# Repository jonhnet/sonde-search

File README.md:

# sonde-search
a couple dorks trying to break into the easiest hobby ever

## Conda environment

The conda environment is pinned in `environment.yml` (versions only, no build hashes — portable across platforms).

Create a fresh env:
```bash
mamba env create -n sondesearch -f environment.yml
```

Sync an existing env to match (adds new deps, removes removed ones):
```bash
mamba env update -n sondesearch -f environment.yml --prune
```

After changing deps locally, regenerate the lock and commit it:
```bash
conda env export --no-builds | sed '/^prefix:/d' > environment.yml
```

## Tests

From the repo root:
```bash
pytest
```
Each subproject (`aprs-backhaul/`, `analyzers/paneltest/`, `website/backend/`) can also be tested independently from its own directory.

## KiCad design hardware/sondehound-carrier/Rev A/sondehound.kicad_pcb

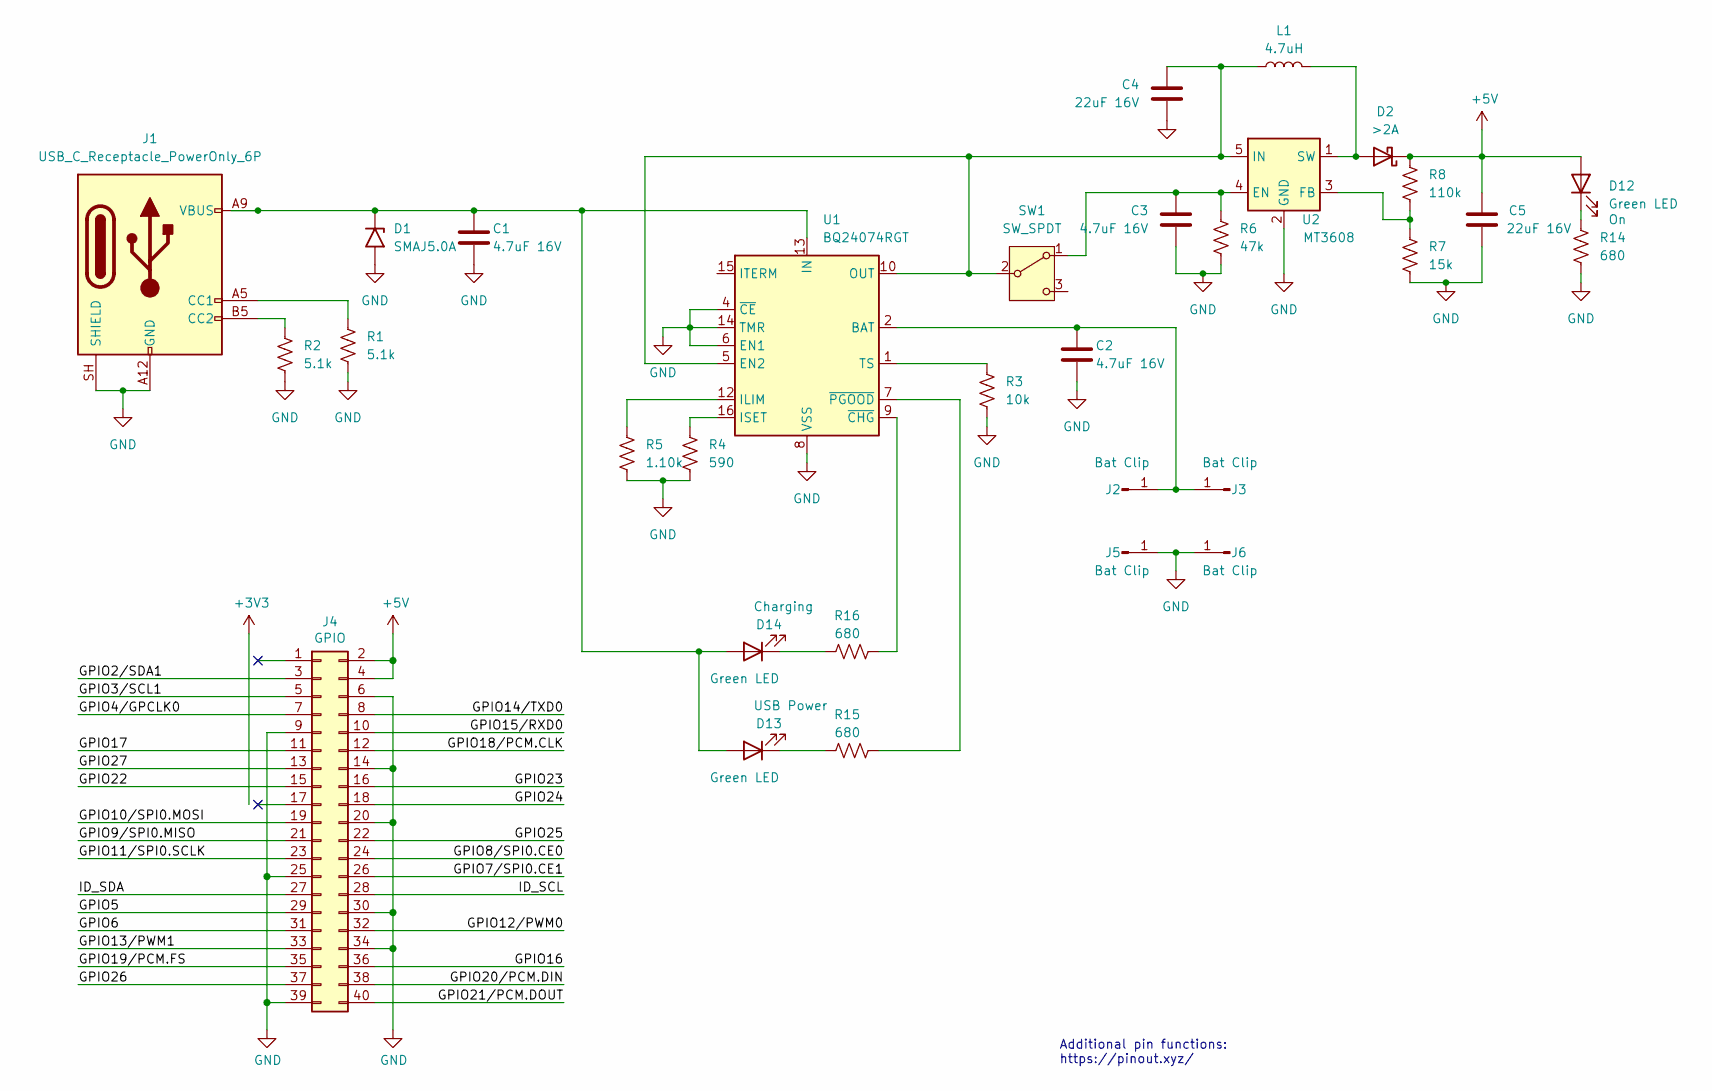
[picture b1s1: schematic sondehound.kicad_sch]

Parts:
C1, C2, C3: 4.7uF 16V; C_0603_1608Metric_Pad1.08x0.95mm_HandSolder
C4, C5: 22uF 16V; C_1210_3225Metric_Pad1.33x2.70mm_HandSolder
D1: SMAJ5.0A; D_SMA
D2: >2A; D_SMA_Handsoldering
D12, D13, D14: Green LED; LED_0603_1608Metric_Pad1.05x0.95mm_HandSolder
J1: USB_C_Receptacle_PowerOnly_6P; USB_C_Receptacle_GCT_USB4125-xx-x_6P_TopMnt_Horizontal
J2, J3, J5, J6: Bat Clip; BatteryClip_Keystone_54_D16-19mm
J4: GPIO; PinSocket_2x20_P2.54mm_Vertical
L1: 4.7uH; L_Chilisin_BMRB00050518-B
R1, R2: 5.1k; R_0603_1608Metric_Pad0.98x0.95mm_HandSolder
R3: 10k; R_0603_1608Metric_Pad0.98x0.95mm_HandSolder
R4: 590; R_0603_1608Metric_Pad0.98x0.95mm_HandSolder
R5: 1.10k; R_0603_1608Metric_Pad0.98x0.95mm_HandSolder
R6: 47k; R_0603_1608Metric_Pad0.98x0.95mm_HandSolder
R7: 15k; R_0603_1608Metric_Pad0.98x0.95mm_HandSolder
R8: 110k; R_0603_1608Metric_Pad0.98x0.95mm_HandSolder
R14, R15, R16: 680; R_0603_1608Metric_Pad0.98x0.95mm_HandSolder
SW1: SW_SPDT; SS12D10G6
U1: BQ24074RGT; VQFN-16-1EP_3x3mm_P0.5mm_EP1.6x1.6mm
U2: MT3608; SOT-23-6

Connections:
+5V: C5.1, D2.1 (K), D12.2 (A), J4.2, J4.4, R8.1
/GPIO2/SDA1: J4.3
/GPIO3/SCL1: J4.5
/GPIO4/GPCLK0: J4.7
/GPIO5: J4.29
/GPIO6: J4.31
/GPIO7/SPI0.CE1: J4.26
/GPIO8/SPI0.CE0: J4.24
/GPIO9/SPI0.MISO: J4.21
/GPIO10/SPI0.MOSI: J4.19
/GPIO11/SPI0.SCLK: J4.23
/GPIO12/PWM0: J4.32
/GPIO13/PWM1: J4.33
/GPIO14/TXD0: J4.8
/GPIO15/RXD0: J4.10
/GPIO16: J4.36
/GPIO17: J4.11
/GPIO18/PCM.CLK: J4.12
/GPIO19/PCM.FS: J4.35
/GPIO20/PCM.DIN: J4.38
/GPIO21/PCM.DOUT: J4.40
/GPIO22: J4.15
/GPIO23: J4.16
/GPIO24: J4.18
/GPIO25: J4.22
/GPIO26: J4.37
/GPIO27: J4.13
/ID_SCL: J4.28
/ID_SDA: J4.27
GND: C1.1, C2.1, C3.2, C4.2, C5.2, D1.2 (A2), J1.A12 (GND), J1.B12 (GND), J1.SH (SHIELD), J4.6, J4.9, J4.14, J4.20, J4.25, J4.30, J4.34, J4.39, J5.1 (Pin_1_1), J6.1 (Pin_1_1), R1.2, R2.2, R3.2, R4.2, R5.2, R6.2, R7.2, R14.2, U1.4 (~CE), U1.6 (EN1), U1.8 (VSS), U1.14 (TMR), U1.17 (VSS), U2.2 (GND)
unnamed: C1.2, D1.1 (A1), D13.2 (A), D14.2 (A), J1.A9 (VBUS), J1.B9 (VBUS), U1.13 (IN)
unnamed: D2.2 (A), L1.2, U2.1 (SW)
unnamed: D12.1 (K), R14.1
unnamed: D13.1 (K), R15.1
unnamed: D14.1 (K), R16.1
unnamed: J1.A5 (CC1), R1.1
unnamed: J1.B5 (CC2), R2.1
unnamed: C2.2, J2.1 (Pin_1_1), J3.1 (Pin_1_1), U1.2 (BAT), U1.3 (BAT)
unnamed: C3.1, R6.1, SW1.1 (A), U2.4 (EN)
unnamed: C4.1, L1.1, SW1.2 (B), U1.5 (EN2), U1.10 (OUT), U1.11 (OUT), U2.5 (IN)
unnamed: R5.1, U1.12 (ILIM)
unnamed: R4.1, U1.16 (ISET)
unnamed: R3.1, U1.1 (TS)
unnamed: R16.2, U1.9 (~CHG)
unnamed: R15.2, U1.7 (~PGOOD)
unnamed: R7.1, R8.2, U2.3 (FB)

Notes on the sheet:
Additional pin functions: https://pinout.xyz/

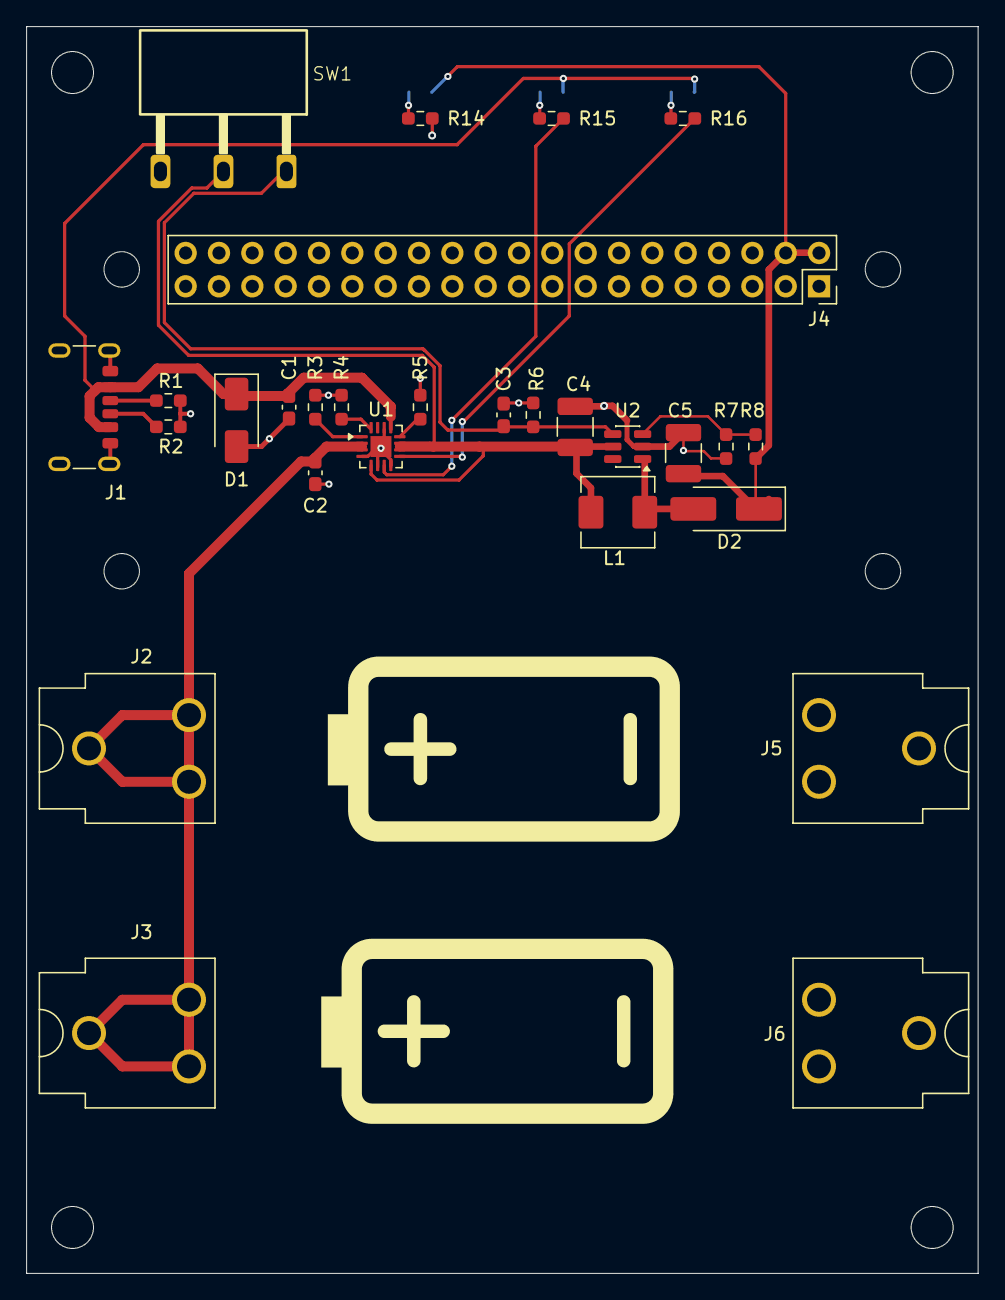
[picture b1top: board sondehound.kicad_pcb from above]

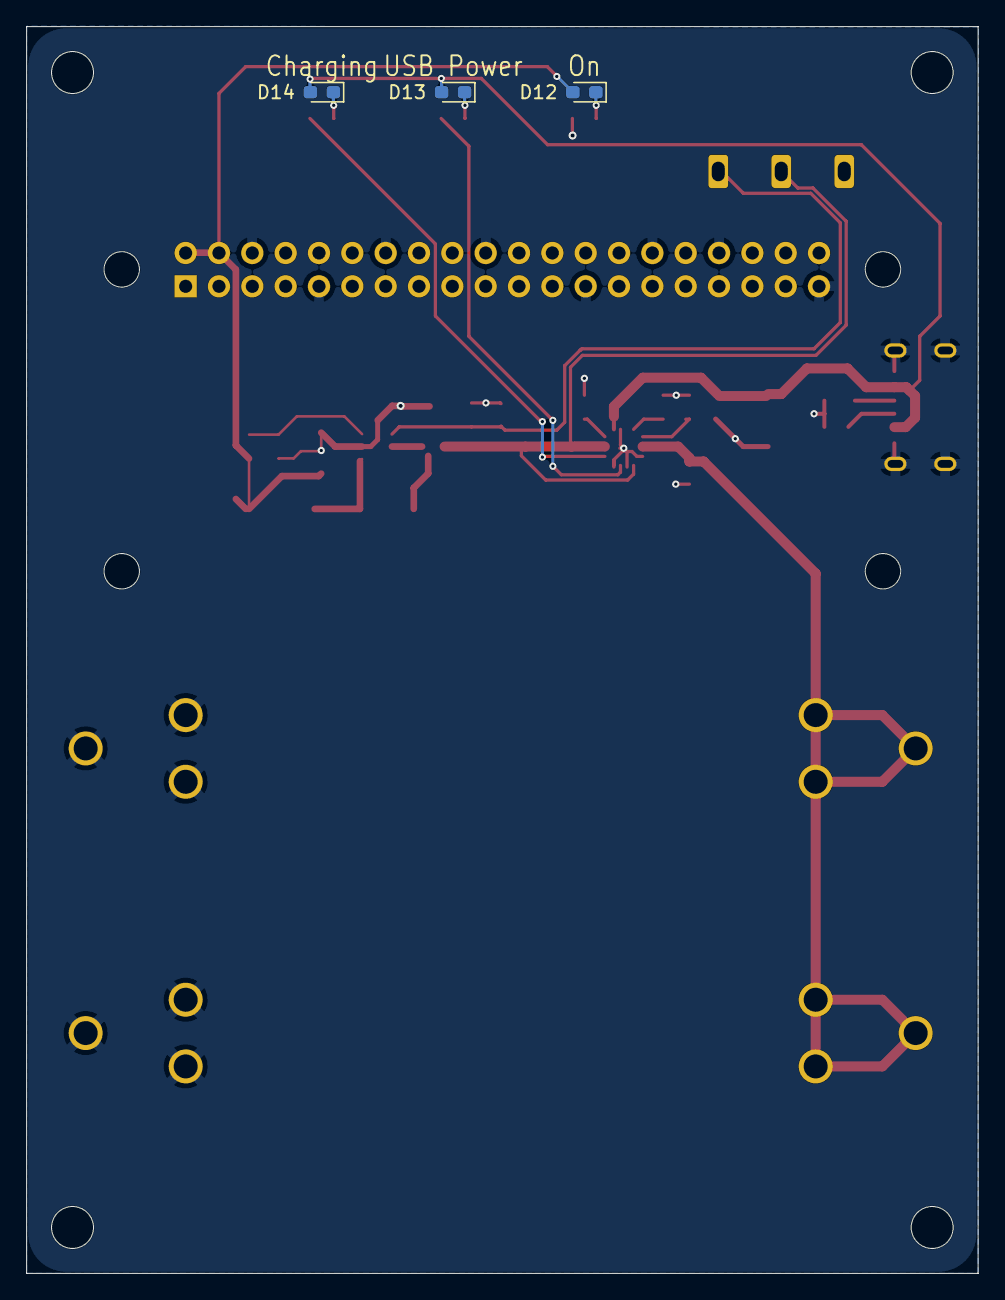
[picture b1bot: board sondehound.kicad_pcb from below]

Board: 2 copper layers, 72.5 x 95.0 mm, 35 parts (3 on the bottom side), 18 nets.

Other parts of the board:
MH1, MH2, MH3, MH4: MountingHole_2.7mm_M2.5

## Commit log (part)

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2023-07-17 remove unneeded dep
2023-07-20 Sonde email notifier: plot line to site of last reception
2023-07-21 Add gitignore
2023-08-09 tableize the email output
2023-08-09 add html and body tags
2023-09-03 Email notifier: make more resilient to elevation API errors
2023-10-26 add attach option for email notifier
2023-11-16 switch website backend from encrypted tokens to uuids combined with backend state
2023-11-17 Basic framework of new sondesearch frontend; not complete
2023-11-17 web site front end: table generation; delete link; loading icon
2023-11-17 add loading icon for deletion
2023-11-18 add new test of two accounts in use at once
2023-11-18 Add uswgi service file
2023-11-18 Changes to play nicely with cloudfront
2023-11-18 better about page
2023-11-19 More web site setup
2023-11-19 web site updates
2023-11-19 Email notifier updates
2023-11-19 copy edit
2023-11-23 more copywriting
2023-11-24 copyedits
2023-11-25 Update tar-to-parquet converter
2023-11-28 Move data-wrangling scripts into a new directory
2023-11-28 Add raw data page to web site
2023-11-29 Some more vscodeification
2023-12-03 Improve scripts to to use web data
    * Automatically download latest data from the web, cached in /tmp
    * Re-generate maps with larger data sets and publish to vault
2023-12-03 reduce h2 margin
2023-12-03 add stub for receiver analyzer page
2023-12-03 Update calendar generator
    * Use new data cache library
    * Generate webp
2023-12-03 Updates to about page
2023-12-06 Move email notifier script into website/backend
2023-12-07 notifier email: remove support for attachments
    We're all-in on the map being a link to an external web site
2023-12-10 type fixes; thanks, pylance!
2023-12-12 Change notifier to use database config rather than static config
2023-12-12 Small fixups to notifier script
2023-12-12 fix paths
2023-12-12 Change lookback to 6 hours
2023-12-14 Update API of oneclick unsubscribe
2023-12-14 Set notifier management cookie to expire in 1 year
2023-12-14 Record the time of subscriptions and unsubscriptions
2023-12-14 Notifier management: handle errors more gracefully
2023-12-15 Notifier: handle receivers with no lat/lons
2023-12-16 Added first-find story
2023-12-16 add first-find story to the web site
2023-12-18 add opacity to heatmaps
2023-12-18 Notifier signup: get rid of some annoying visual artifacts
2023-12-19 spelling
2023-12-19 fix vscode warnings
2023-12-19 Notifier table creator: put newest tables first
    That way the new tables can be created before the attempt to create existing tables throws an exception
2023-12-20 Notifier: change back end to support subscription editing
    Also, add test
2023-12-23 Refactor notifier tables; fix to be insensitive to email case
    * Switch table client creation from cheesily adding fields to an object passed in, to return an actual class containing tables as fields.
    * When creating a user, write both the email-as-given and email-converted-to-lowercase to the user entry. Create an index based on the lowercase email that is used to look up user entries. Fixes a bu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
    * Adjust one of the unit tests to test for changing email case and validate that the lookup is insensitive to it
    * Add utility that prints users and their subscriptions, and adds a lowercase f
2023-12-23 Notifier: add get_notification_history to exposed API
2023-12-23 notifier api: more json fixes for history
2023-12-24 Add notification history display to notifier management page
2023-12-25 notifier: better debug output
2024-01-10 Switch map URL to maps.sondesearch.lectrobox.com
2024-01-25 Updates to notifier management front-end
    * Switch to async/await fetch rather than jquery ajax to get backend data; both makes the code cleaner and fixes the bug that history should not be rendered until config arrives, even if history happ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
    * Try to reduce accidental deletion-clicks by moving the handler to the inner rather than outer button
2024-01-27 fix typo
2024-01-27 improve error reporting for bad sondehub data
2024-01-31 improve test to make pylance happy
2024-01-31 Change sonde notifier sleep policy
    Only sleep after an email sent, not after each subscription is considered.
2024-02-02 add date to first-find story
2024-02-02 notifier signup: fix visual bug on phones
2024-02-11 show_subs improvement: sort by both sub and unsub time
2024-02-11 email notifier: graceful handling of data without v/h velocity
2024-02-12 clarify receivers
2024-03-03 add SMA antenna
2024-03-14 show uuid with subscription summary
2024-05-04 refactor sondehub retriever into util
    Previously, the sondehub retriever was part of the email notifier. I'd like to use it from other parts of the code, so this commit refactors it into util.
2024-05-05 KMLifier: fix typo
2024-05-05 Add simplekml to requirements
2024-05-12 Ensure sonde dataframes have a unique index per record
2024-05-26 Add first version of script that finds pairs of landings close together
    Also add notebook used for development
2024-05-30 add user-agent to OSM queries
2024-10-14 Fix for contextily 1.6.2 where axes are no longer set equal aspect ratio for you
2024-11-11 fixes for v2 api
2024-11-11 Fixes to CORS config
2024-11-11 Change email verifier to use a new auth landing page
2024-11-11 Add backcompat for old email links
2024-11-12 Option to show sondesearch notifier cancellations
2024-11-12 logging
2024-11-12 tinkering with closest-landing analyzer
2024-11-12 wordsmithing
2024-11-12 more logging
2024-11-13 Dev mode and map preview
    Lots of changes:
    * Pull the thread all the way through to run a dev version of the web site (locally served with Jekyll) with a dev version of the backend (locally served via cherrypy). Add a "dev.sh" script that run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
    * add new map preview of notification area from the setup page
2024-11-13 Make cursor look clickable over map icon
2024-11-13 Change map icon
2024-12-26 Show year-over-year changes in addition to by-month calendar
2025-01-11 Update parquet files with 2024 data
2025-01-11 update heatmaps for 2024
2025-10-18 Add ground-reception plotting utility
    Add a utility that plots the best estimate of lat, lon and altitude for sondes that have ground reception, and therefore have many points received while on the ground.
    TODO: Refactor some of the copy-pasted code into a new file of utilities that's shared by both the offline analyzers and the online service
2025-10-19 need requirements.txt to be in same dir as Dockerfile
2025-10-19 missing binaries in podman dockerfile
2025-10-19 single LL text box
2025-10-19 bugfix 3
2025-10-19 re-fix persistence bug
2025-10-19 relative paths
2025-10-19 update dockefile for statics
2025-10-19 split up many-tile downloads. viewshed progress indicator
2025-10-19 fix SRTM1 fallback
2025-10-19 cache SRTM1 tiles better
2025-10-19 stable tile based caching with debug button
2025-10-19 favorites for optimize page
2025-11-15 change max-dist dynamically when switching units
2025-11-15 vscode preferences update
2025-11-15 make stuff flake8-clean
2025-11-16 refactor KML generator so there's also a CLI tool
2025-11-16 make interactive landing calendar site
    Refactored landing-calendar code into the shraed library so there can be both a CLI tool and a backend tool. created interactive map to specify bounds and generate arbitrary calendars. BOOM!
2025-11-18 proper em dashes
2025-11-18 try again to prevent spurious unsubscribes
2025-11-18 update uwsgi config to be threaded; delete obsolete files
2025-11-18 more uwsgi config changes
2025-11-18 more uwsgi
2025-11-18 UI improvements to calendar generator
2025-11-19 better subject lines for email notifier
2025-11-19 Email notifier adjustments
2025-11-20 don't compute descent with baloons going up
2025-11-20 some refactoring to ensure the JS library is used consistently
2025-11-24 Another attempt at getting emails right with no negative radius
2025-11-24 more ground reception reporting improvements
2025-11-24 describe ground reception plots in web page docs
2025-11-25 HTML-escape user input
2025-11-25 delegate calendar generation to a subprocess so the memory is recovered
2025-11-27 Fix elevation API issues
    * Use USGS first, then fall back to worldwide datasets, for worldwide coverage
    * Change "if elev:" to "if elev is not None" to properly work in places with 0 elevation
    * Add test suite
2025-11-27 add type annotations
2025-11-28 improve ground reception detection
    Previously we'd find the first point with a near-zero velocity and take every point from there to the end. Now we take the largest contiguous block of near-zero velocity that ends with the final fram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
2025-11-28 improve format of ground reception map
    make axes fall on regularl intervals; ensure 0 is always a tick mark; update example image on web site
2025-11-29 more minor fixups for ground reception map
2025-12-03 more ground reception stats
    show distance from lat-lon of last received frame to average of all ground points
2025-12-03 tiny filename change
2025-12-03 improve wording
2025-12-03 better USGS API debug
2025-12-04 better logging of elevation API calls
2025-12-21 switch contextily cache dir to be configured with file
    there are 4 diff places I'd have to set the env var
2025-12-22 Finally fix phantom unsubscriptions from email scanners
    Just emailing a link that has authorization to mutate user state was causing virus scanners to click randomly on email links, sometimes causing unsubscriptions without user action.
    Claude suggested what it called the "magic link" pattern: when a user requests a signup, the backend gives their browser a token. It also emails them a second token. The user token, needed to modify 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
    Email scanners no longer can access user state because they don't have the token hidden in the browser. Users also can't spam email addresses they don't own because they won't have the token that arri
2026-05-26 pirate: add ka9q-radio + auto_rx Airspy receiver installer
    Generic setup.sh that builds pinned ka9q-radio + radiosonde_auto_rx and
    configures an Airspy-fed receiver; takes a station name so multiple
    receivers can coexist on a LAN. No site-specific data baked in.
2026-05-29 Tune buck characterizer DMM defaults
2026-05-29 Add buck comparison matrix tool
2026-05-30 text updates
2026-06-02 pirate: make setup idempotent and station-configurable
2026-06-02 pirate: document the off-grid goal and Pi 4 vs Zero 2 W hardware story
    Add a "Goal" section laying out the solar-panel → LiFePO4 → buck → PiDog2 v0.7
    → Pi 4 + Airspy chain, framed as a coverage-vs-survivability tradeoff (we
    could oversize the panel and run always-on; we'd rather give up some coverage
    so the site rides out poor solar stretches). Replace the hedged "Zero 2 W is
    marginal" hardware bullet with the actual test result: auto_rx's tune
    handshake to radiod timed out even at 30s on a Zero 2 W, because radiod's
2026-06-03 Add Pirate LTE and WireGuard setup
2026-06-03 Archive paneltest solar run
2026-06-03 stop ignoring csvs so i don't delete data accidentally
2026-06-03 Clarify paneltest load voltage choice
